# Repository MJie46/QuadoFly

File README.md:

# QuadoFly
>
#### 尺寸40*45mm
#### stm32f103主控
#### IP5306集成电池充放电管理和升压输出
#### 双DRV8833输出
#### 4通道pwm
#### MPU6050
#### 0.96寸OLED接口
#### 板载一个蓝牙模块
#### 引出一路GPIO，一路IIC

### 软件开发中，板子可以做得更迷你，更多是将这个板子作为无人机，遥控车的开发板，所以引出多个接口，板子体积增大，待软硬完善后再重新设计专用的板子...

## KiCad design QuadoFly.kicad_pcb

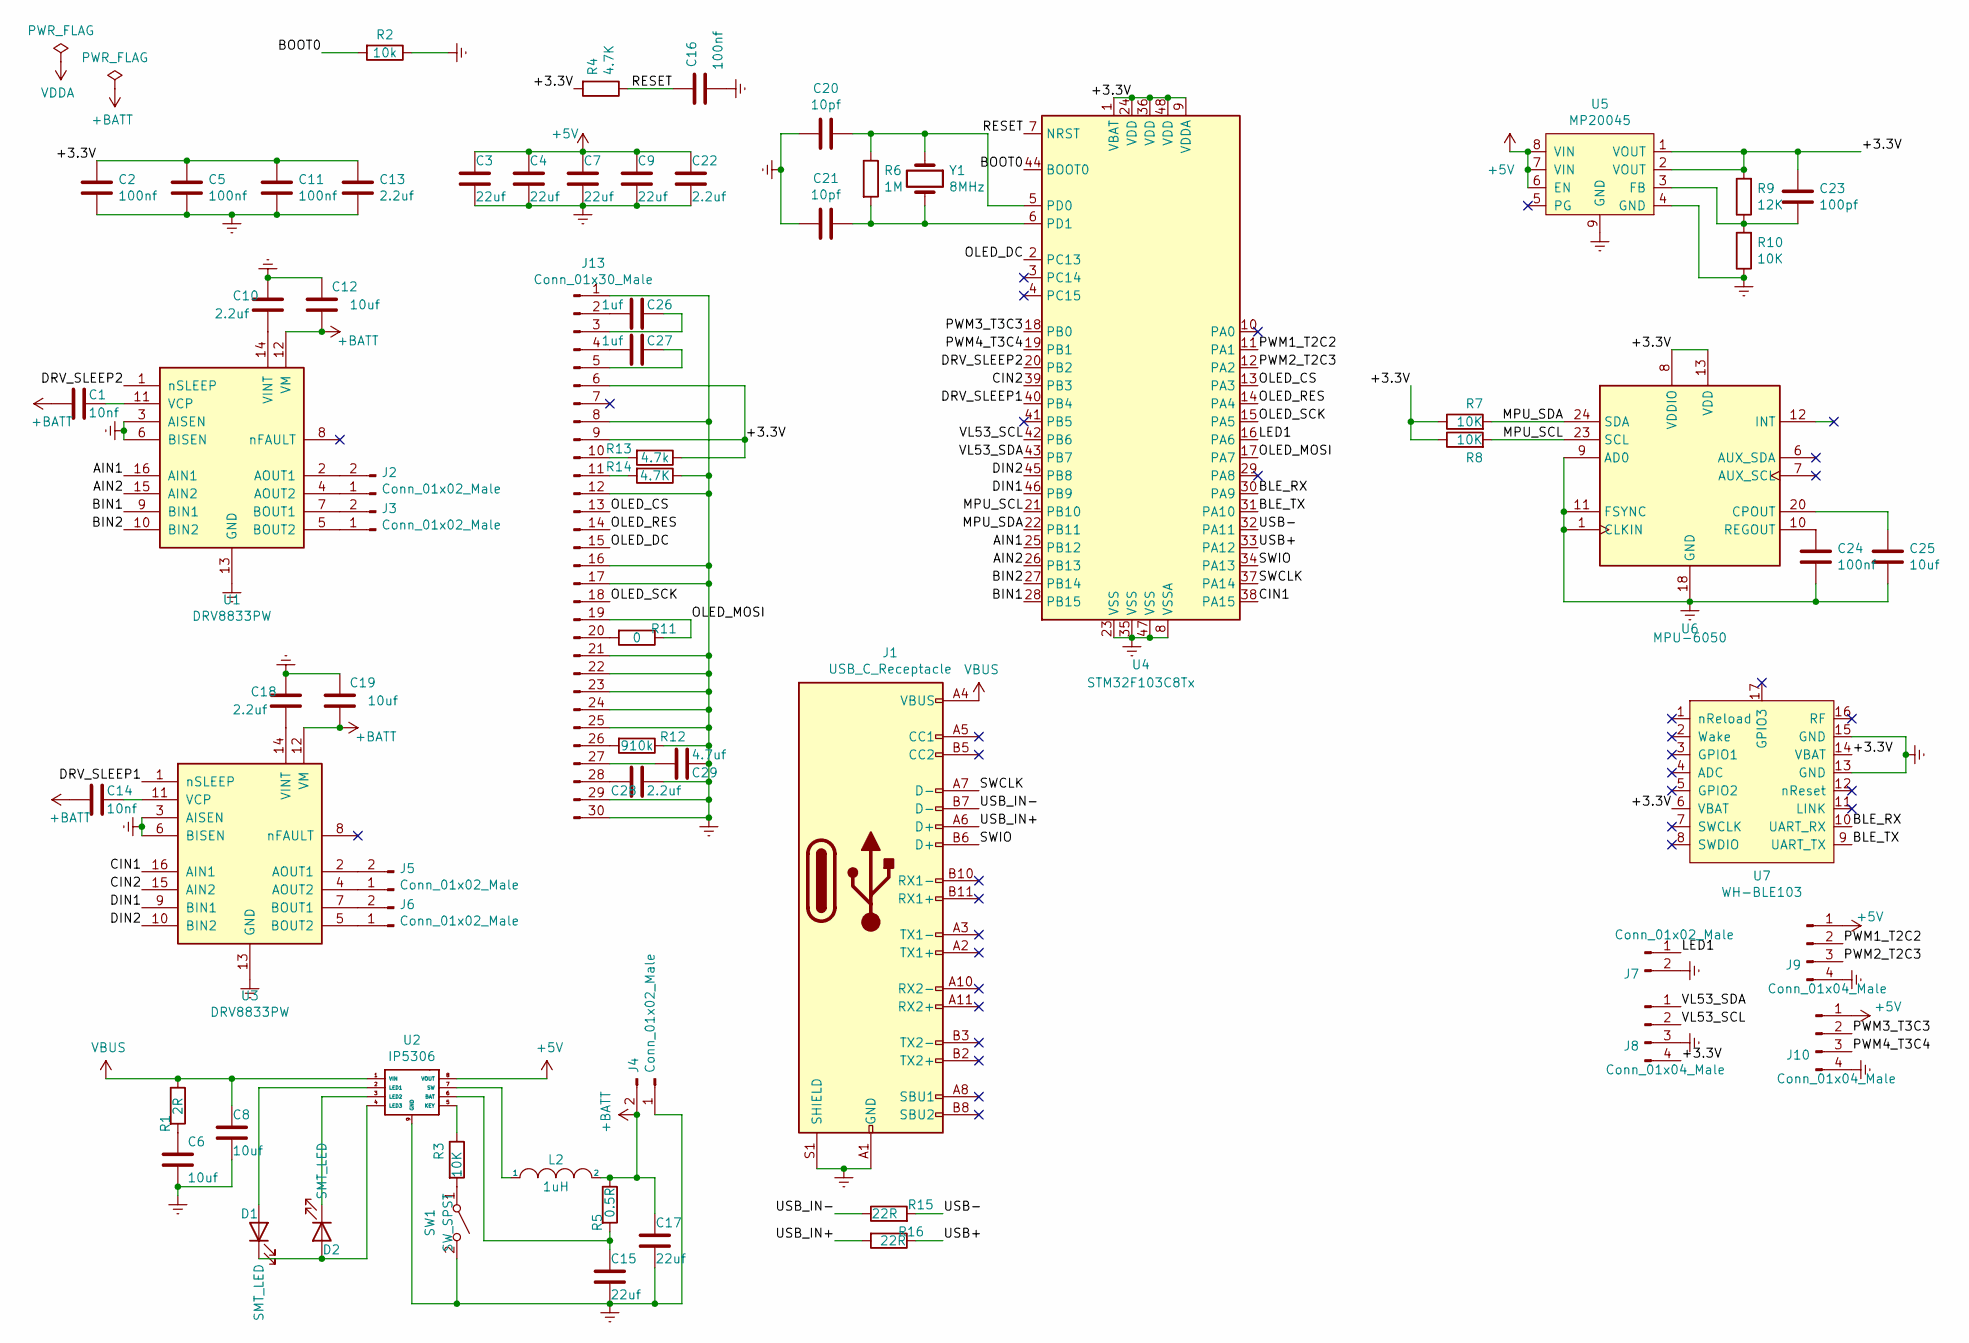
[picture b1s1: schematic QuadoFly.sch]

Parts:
C1, C14: 10nf; C_0603_1608Metric_Pad1.05x0.95mm_HandSolder
C2, C5, C11, C16, C24: 100nf; C_0603_1608Metric_Pad1.05x0.95mm_HandSolder
C3, C4, C7, C9, C15, C17: 22uf; C_0603_1608Metric_Pad1.05x0.95mm_HandSolder
C6, C8, C12, C19, C25: 10uf; C_0603_1608Metric_Pad1.05x0.95mm_HandSolder
C10, C13, C18, C22, C28: 2.2uf; C_0603_1608Metric_Pad1.05x0.95mm_HandSolder
C20, C21: 10pf; C_0603_1608Metric_Pad1.05x0.95mm_HandSolder
C23: 100pf; C_0603_1608Metric_Pad1.05x0.95mm_HandSolder
C26, C27: 1uf; C_0603_1608Metric_Pad1.05x0.95mm_HandSolder
C29: 4.7uf; C_0603_1608Metric_Pad1.05x0.95mm_HandSolder
D1, D2: SMT_LED; LED_0603_1608Metric
J1: USB_C_Receptacle; USB_C_Receptacle_XKB_U262-16XN-4BVC11
J2, J3, J4, J5, J6, J7: Conn_01x02_Male; PinHeader_1x02_P2.00mm_Vertical
J8, J9, J10: Conn_01x04_Male; PinHeader_1x04_P2.00mm_Vertical
J13: Conn_01x30_Male; FPC_1x30-0.7mm
L2: 1uH; L_Wuerth_HCI-7030
R1: 2R; R_0603_1608Metric_Pad1.05x0.95mm_HandSolder
R2: 10k; R_0603_1608Metric_Pad1.05x0.95mm_HandSolder
R3, R7, R8, R10: 10K; R_0603_1608Metric_Pad1.05x0.95mm_HandSolder
R4, R14: 4.7K; R_0603_1608Metric_Pad1.05x0.95mm_HandSolder
R5: 0.5R; R_0603_1608Metric_Pad1.05x0.95mm_HandSolder
R6: 1M; R_0603_1608Metric_Pad1.05x0.95mm_HandSolder
R9: 12K; R_0603_1608Metric_Pad1.05x0.95mm_HandSolder
R11: 0; R_0603_1608Metric_Pad1.05x0.95mm_HandSolder
R12: 910k; R_0603_1608Metric_Pad1.05x0.95mm_HandSolder
R13: 4.7k; R_0603_1608Metric_Pad1.05x0.95mm_HandSolder
R15, R16: 22R; R_0603_1608Metric_Pad1.05x0.95mm_HandSolder
SW1: SW_SPST; SW_SPST_B3U-1000P
U1, U3: DRV8833PW; TSSOP-16_4.4x5mm_P0.65mm
U2: IP5306; SOIC-8-1EP_3.9x4.9mm_P1.27mm_EP2.29x3mm
U4: STM32F103C8Tx; LQFP-48_7x7mm_P0.5mm
U5: MP20045; SOIC-8-1EP_3.9x4.9mm_P1.27mm_EP2.41x3.3mm
U6: MPU-6050; InvenSense_QFN-24_4x4mm_P0.5mm
U7: WH-BLE103
Y1: 8MHz; Crystal_SMD_TXC_7A-2Pin_5x3.2mm

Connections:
+5V: C3.1, C4.1, C7.1, C9.1, C22.1, J9.1, J10.1, U2.8 (VOUT), U5.6 (EN), U5.7 (VIN), U5.8 (VIN)
+BATT: C1.2, C12.2, C14.2, C17.1, C19.2, J4.2, L2.2, R5.1, U1.12 (VM), U3.12 (VM)
/+3.3V: C2.1, C5.1, C11.1, C13.1, C23.1, J8.4, J13.6, J13.9, R4.2, R7.1, R8.1, R9.2, R13.1, U4.1 (VBAT), U4.9 (VDDA), U4.24 (VDD), U4.36 (VDD), U4.48 (VDD), U5.1 (VOUT), U5.2 (VOUT), U6.8 (VDDIO), U6.13 (VDD), U7.6 (VBAT), U7.14 (VBAT)
/AIN1: U1.16 (AIN1), U4.25 (PB12)
/AIN2: U1.15 (AIN2), U4.26 (PB13)
/BIN1: U1.9 (BIN1), U4.28 (PB15)
/BIN2: U1.10 (BIN2), U4.27 (PB14)
/BLE_RX: U4.30 (PA9), U7.10 (UART_RX)
/BLE_TX: U4.31 (PA10), U7.9 (UART_TX)
/BOOT0: R2.2, U4.44 (BOOT0)
/CIN1: U3.16 (AIN1), U4.38 (PA15)
/CIN2: U3.15 (AIN2), U4.39 (PB3)
/DIN1: U3.9 (BIN1), U4.46 (PB9)
/DIN2: U3.10 (BIN2), U4.45 (PB8)
/DRV_SLEEP1: U3.1 (nSLEEP), U4.40 (PB4)
/DRV_SLEEP2: U1.1 (nSLEEP), U4.20 (PB2)
/LED1: J7.1, U4.16 (PA6)
/MPU_SCL: R8.2, U4.21 (PB10), U6.23 (SCL)
/MPU_SDA: R7.2, U4.22 (PB11), U6.24 (SDA)
/OLED_CS: J13.13, U4.13 (PA3)
/OLED_DC: J13.15, U4.2 (PC13)
/OLED_MOSI: J13.19, R11.1, U4.17 (PA7)
/OLED_RES: J13.14, U4.14 (PA4)
/OLED_SCK: J13.18, U4.15 (PA5)
/PWM1_T2C2: J9.2, U4.11 (PA1)
/PWM2_T2C3: J9.3, U4.12 (PA2)
/PWM3_T3C3: J10.2, U4.18 (PB0)
/PWM4_T3C4: J10.3, U4.19 (PB1)
/RESET: C16.1, R4.1, U4.7 (NRST)
/SWCLK: J1.A7 (D-), U4.37 (PA14)
/SWIO: J1.B6 (D+), U4.34 (PA13)
/USB+: R16.1, U4.33 (PA12)
/USB-: R15.2, U4.32 (PA11)
/USB_IN+: J1.A6 (D+), R16.2
/USB_IN-: J1.B7 (D-), R15.1
/VL53_SCL: J8.2, U4.42 (PB6)
/VL53_SDA: J8.1, U4.43 (PB7)
Earth: C2.2, C3.2, C4.2, C5.2, C6.2, C7.2, C8.2, C9.2, C10.1, C11.2, C12.1, C13.2, C15.2, C16.2, C17.2, C18.1, C19.1, C20.2, C21.2, C22.2, C24.2, C25.2, C28.1, C29.1, J1.A1 (GND), J1.A12 (GND), J1.B1 (GND), J1.B12 (GND), J1.S1 (SHIELD), J4.1, J7.2, J8.3, J9.4, J10.4, J13.1, J13.8, J13.12, J13.16, J13.17, J13.21, J13.22, J13.23, J13.24, J13.25, J13.29, J13.30, R2.1, R10.1, R12.1, R14.1, SW1.2 (B), U1.3 (AISEN), U1.6 (BISEN), U1.13 (GND), U2.9 (GND), U3.3 (AISEN), U3.6 (BISEN), U3.13 (GND), U4.8 (VSSA), U4.23 (VSS), U4.35 (VSS), U4.47 (VSS), U5.4 (GND), U5.9 (GND), U6.1 (CLKIN), U6.9 (AD0), U6.11 (FSYNC), U6.18 (GND), U7.13 (GND), U7.15 (GND)
unnamed: C1.1, U1.11 (VCP)
unnamed: C6.1, R1.2
unnamed: C10.2, U1.14 (VINT)
unnamed: C14.1, U3.11 (VCP)
unnamed: C15.1, R5.2, U2.6 (BAT)
unnamed: C18.2, U3.14 (VINT)
unnamed: C20.1, R6.1, U4.5 (PD0), Y1.1
unnamed: C21.1, R6.2, U4.6 (PD1), Y1.2
unnamed: C23.2, R9.1, R10.2, U5.3 (FB)
unnamed: C24.1, U6.10 (REGOUT)
unnamed: C25.1, U6.20 (CPOUT)
unnamed: C26.1, J13.3
unnamed: C26.2, J13.2
unnamed: C27.1, J13.5
unnamed: C27.2, J13.4
unnamed: C28.2, J13.28
unnamed: C29.2, J13.27
unnamed: D1.1 (K), D2.2 (A), U2.4 (LED3)
unnamed: D1.2 (A), U2.2 (LED1)
unnamed: D2.1 (K), U2.3 (LED2)
unnamed: J2.1, U1.4 (AOUT2)
unnamed: J2.2, U1.2 (AOUT1)
unnamed: J3.1, U1.5 (BOUT2)
unnamed: J3.2, U1.7 (BOUT1)
unnamed: J5.1, U3.4 (AOUT2)
unnamed: J5.2, U3.2 (AOUT1)
unnamed: J6.1, U3.5 (BOUT2)
unnamed: J6.2, U3.7 (BOUT1)
unnamed: J13.10, R13.2
unnamed: J13.11, R14.2
unnamed: J13.20, R11.2
unnamed: J13.26, R12.2
unnamed: L2.1, U2.7 (SW)
unnamed: R3.1, U2.5 (KEY)
unnamed: R3.2, SW1.1 (A)
VBUS: C8.1, J1.A4 (VBUS), J1.A9 (VBUS), J1.B4 (VBUS), J1.B9 (VBUS), R1.1, U2.1 (VIN)

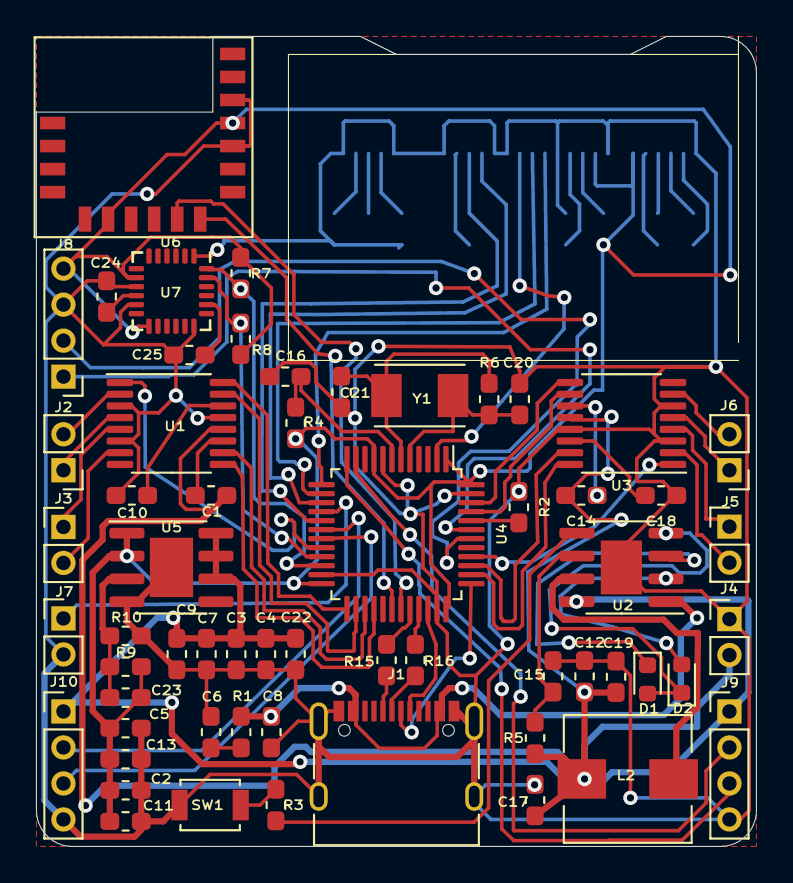
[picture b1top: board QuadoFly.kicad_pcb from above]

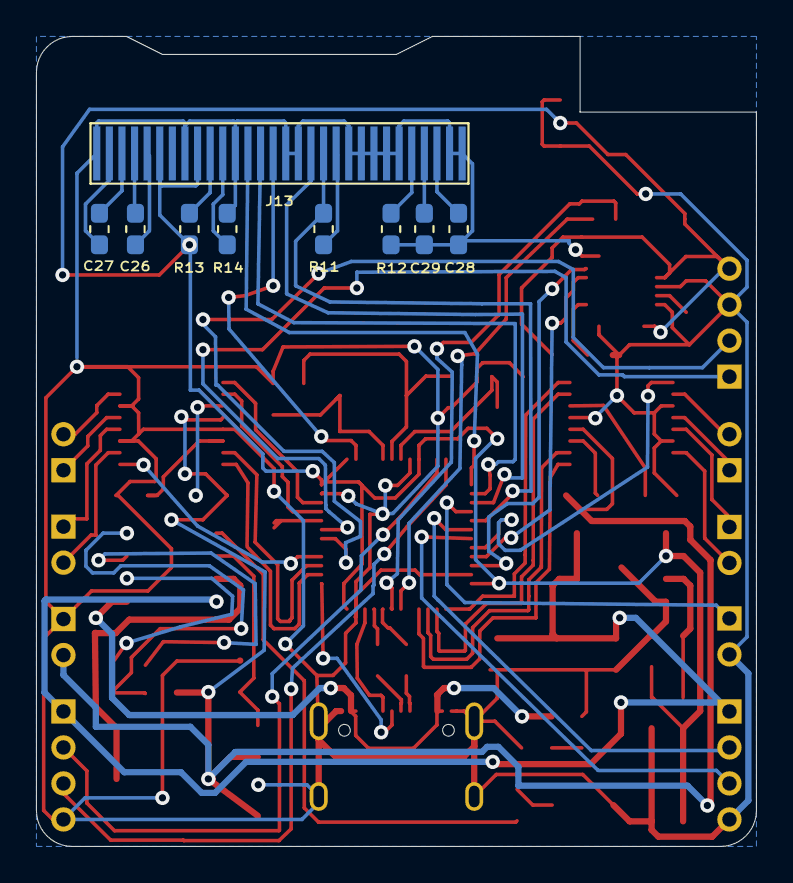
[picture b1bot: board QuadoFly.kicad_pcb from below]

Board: 2 copper layers, 40.0 x 45.0 mm, 68 parts (9 on the bottom side), 74 nets.

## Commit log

2020-10-29 PCB文件
2020-10-29 更新gerber文件，pcb 3d外观
2020-10-30 更新README
